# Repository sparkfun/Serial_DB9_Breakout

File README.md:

Serial_DB9_Breakout
===================

[
*SparkFun Serial DB9 Breakout (BOB-08552)*](https://www.sparkfun.com/products/8552)

A basic breakout board for the Serial DB9 connector. Pins are broken out to standard 0.1" headers. 

Repository Contents
-------------------
* **/Hardware** - All Eagle design files (.brd, .sch)

License Information
-------------------
The hardware is released under [Creative Commons ShareAlike 4.0 International](https://creativecommons.org/licenses/by-sa/4.0/).

Distributed as-is; no warranty is given.

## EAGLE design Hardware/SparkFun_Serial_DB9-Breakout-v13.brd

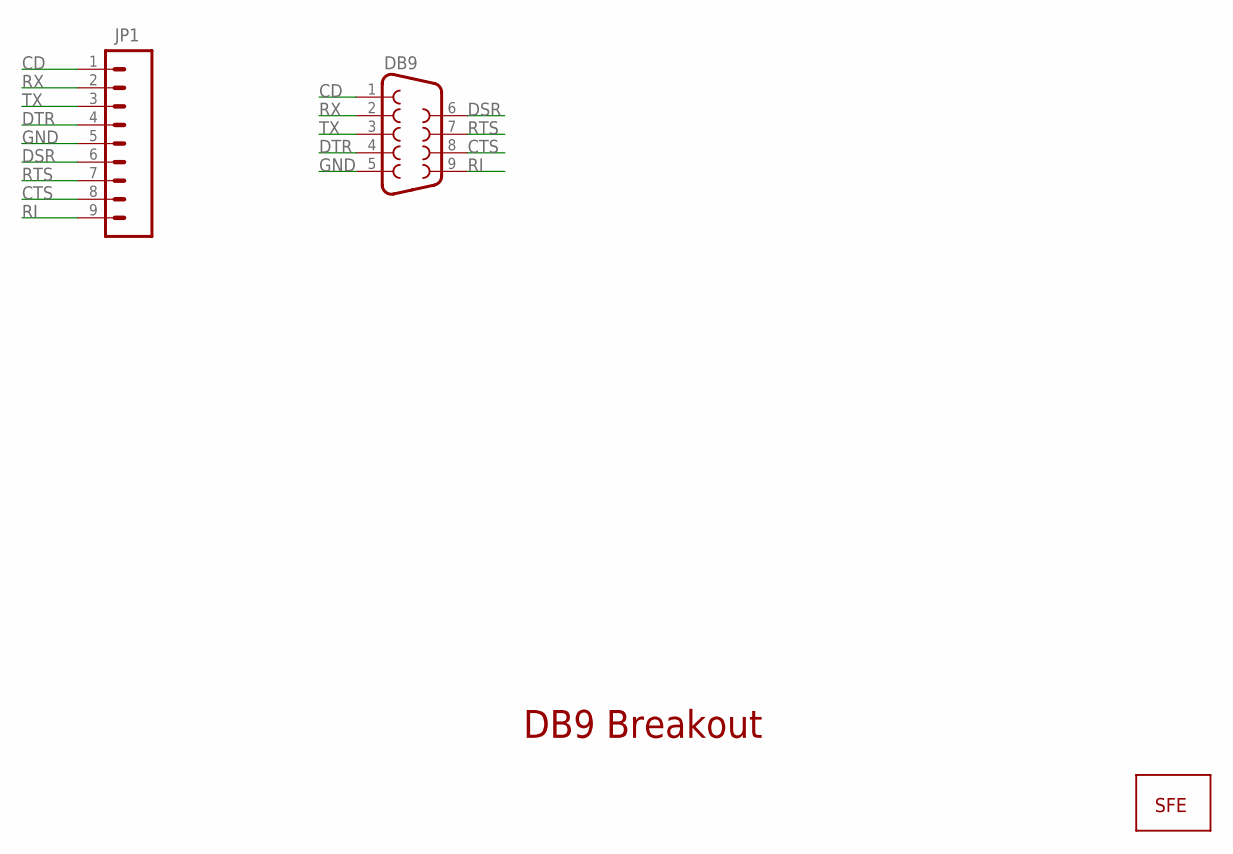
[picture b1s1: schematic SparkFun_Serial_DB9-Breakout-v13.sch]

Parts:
DB9: DB9
JP1: M09; 1X09
U$2: LOGO-SFENEW; SFE-NEW-WEBLOGO

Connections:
CD: DB9.1, JP1.1
CTS: DB9.8, JP1.8
DSR: DB9.6, JP1.6
DTR: DB9.4, JP1.4
GND: DB9.5, JP1.5
RI: DB9.9, JP1.9
RTS: DB9.7, JP1.7
RX: DB9.2, JP1.2
TX: DB9.3, JP1.3

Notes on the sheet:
DB9 Breakout

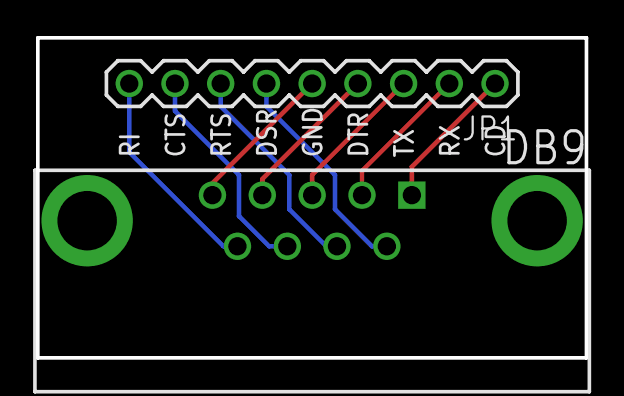
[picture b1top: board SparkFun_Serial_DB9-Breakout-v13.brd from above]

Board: 2 copper layers, 30.5 x 17.8 mm, 3 parts (1 on the bottom side), 9 nets.

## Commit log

2015-01-06 Initial hardware commit
